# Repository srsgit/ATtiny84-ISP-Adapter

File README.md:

PCB to convert from an 6 pin AVR ISP to ATtiny84A Pogo pins.

Eagle 7 schematic and board.

Isolation milling using pcbgcode ULP

Allows in circuit programming via an USBasp straight to the DIP IC.

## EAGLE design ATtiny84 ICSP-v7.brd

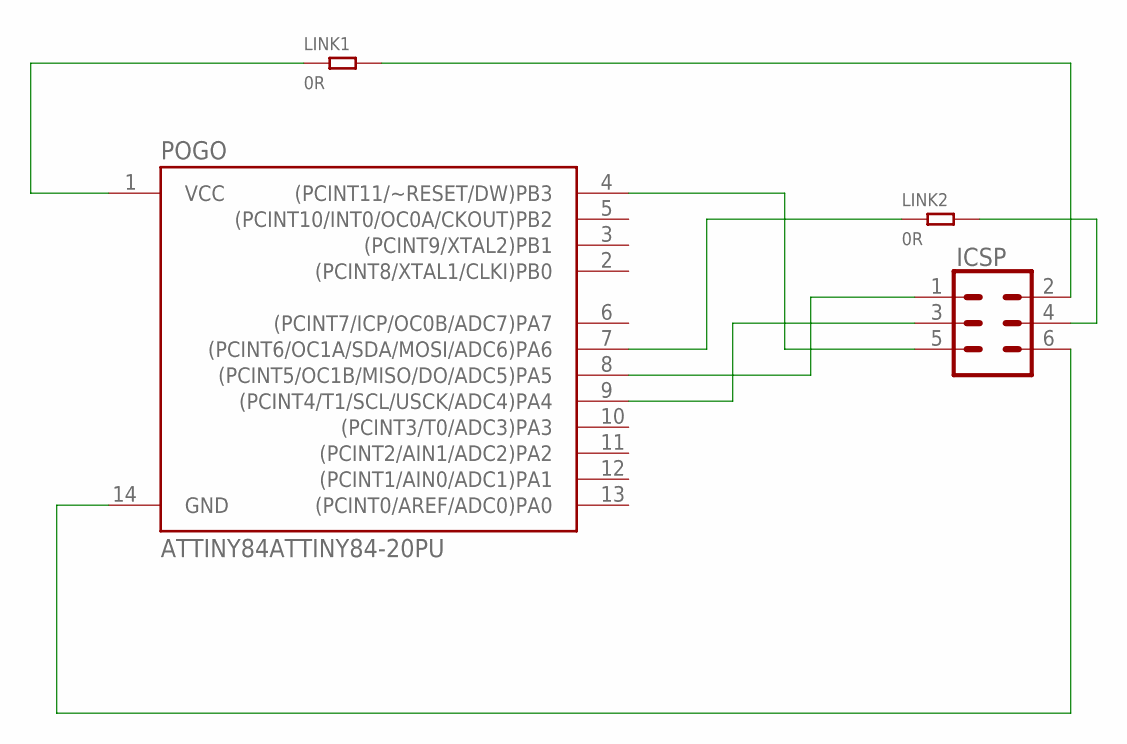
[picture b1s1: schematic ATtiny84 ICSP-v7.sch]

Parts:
ICSP: 2X3-SHROUDED
LINK1, LINK2: 0R; PR-D2.3XL6.5MM
POGO: ATTINY84ATTINY84-20PU; DIP14

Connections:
GND: ICSP.6, POGO.14 (GND)
unnamed: ICSP.1, POGO.8 ((PCINT5/OC1B/MISO/DO/ADC5)PA5)
unnamed: ICSP.3, POGO.9 ((PCINT4/T1/SCL/USCK/ADC4)PA4)
unnamed: ICSP.5, POGO.4 ((PCINT11/~RESET/DW)PB3)
unnamed: ICSP.2, LINK1.2
unnamed: LINK2.1, POGO.7 ((PCINT6/OC1A/SDA/MOSI/ADC6)PA6)
unnamed: LINK1.1, POGO.1 (VCC)
unnamed: ICSP.4, LINK2.2

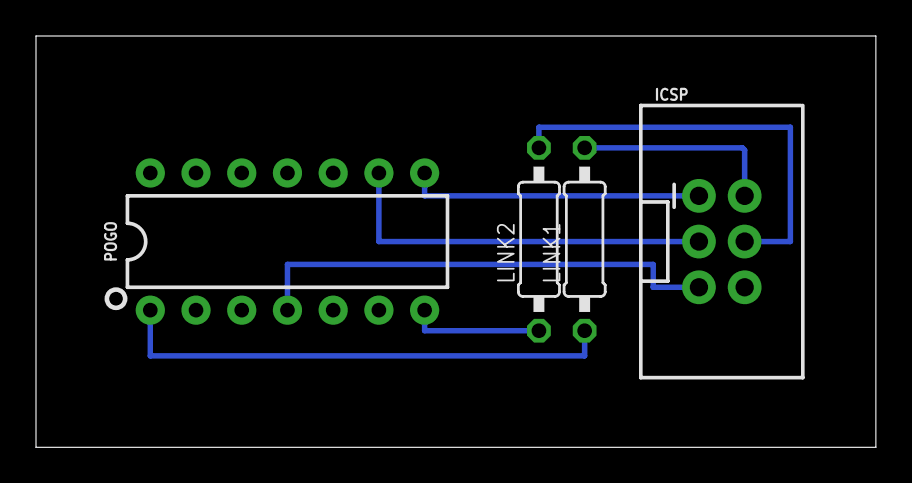
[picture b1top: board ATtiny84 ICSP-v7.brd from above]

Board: 2 copper layers, 46.7 x 22.8 mm, 4 parts (0 on the bottom side), 8 nets.

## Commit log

2018-06-17 Initial commit
    Eagle v7

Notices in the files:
parts and their libraries:
SparkFun-Connectors: Licensing: Creative Commons ShareAlike 4.0 International - https://creativecommons.org/licenses/by-sa/4.0
